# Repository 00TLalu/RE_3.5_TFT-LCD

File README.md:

# RE_3.5_TFT-LCD
 Reverse Engineering PCB 3.5" TFT LCD for arduino uno.

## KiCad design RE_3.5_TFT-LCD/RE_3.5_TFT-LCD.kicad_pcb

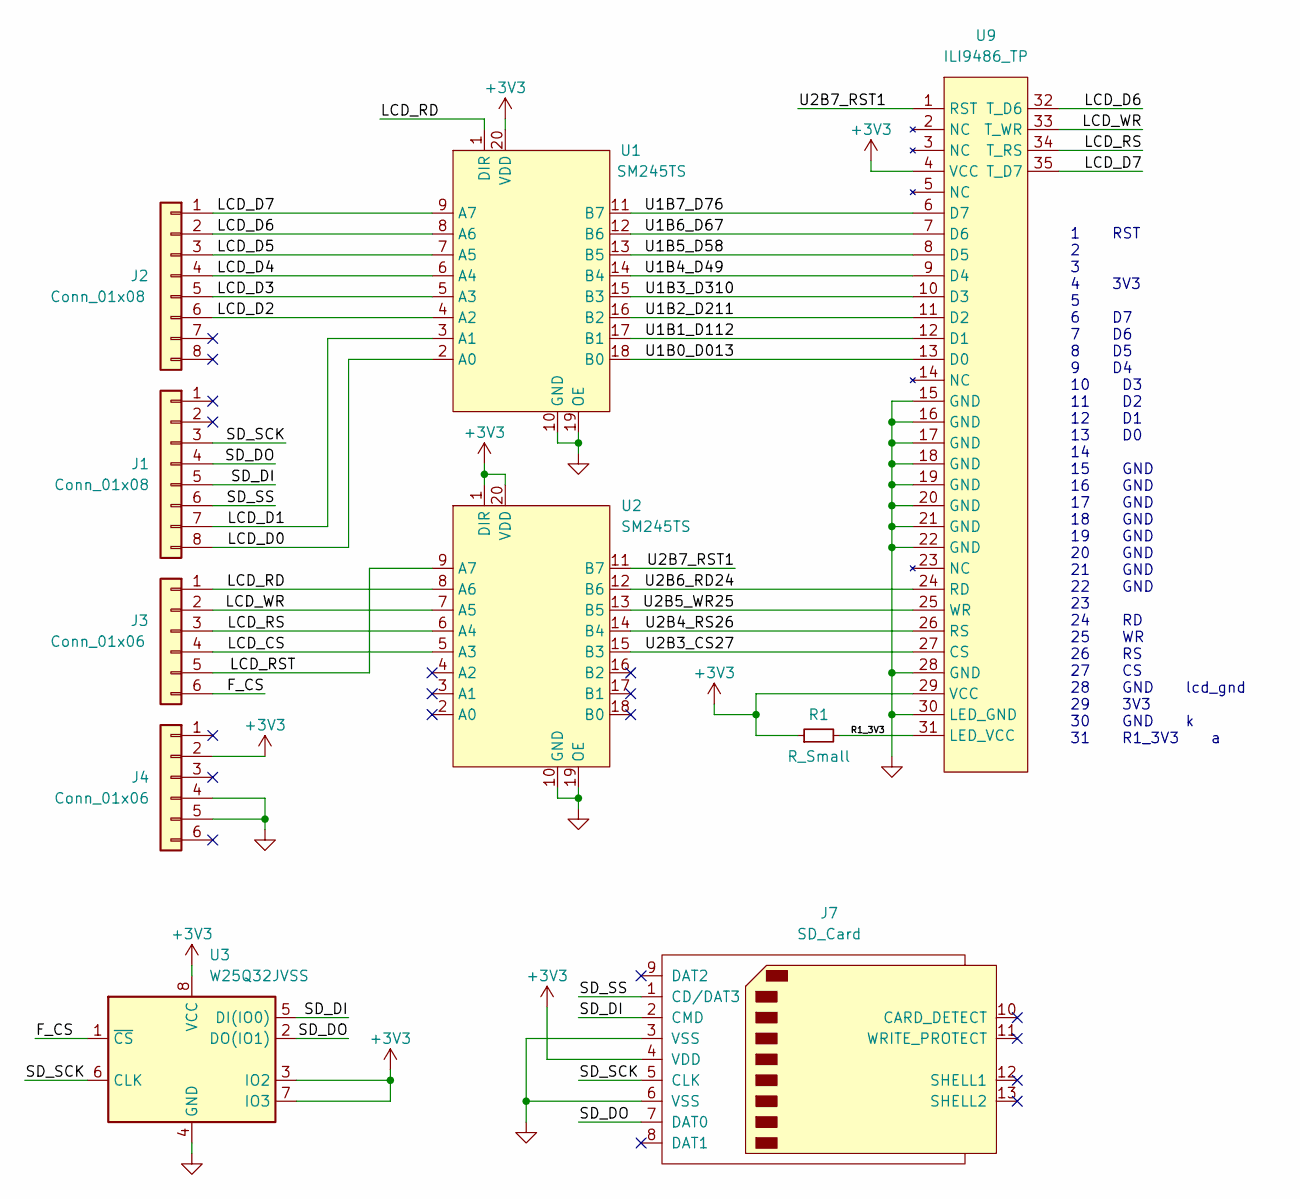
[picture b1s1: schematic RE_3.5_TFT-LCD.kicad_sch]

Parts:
J1, J2: Conn_01x08; PinHeader_1x08_P2.54mm_Vertical
J3, J4: Conn_01x06; PinHeader_1x06_P2.54mm_Vertical
J7: SD_Card; MicroSD
R1: R_Small; R_0402_TL
U1, U2: SM245TS; TSSOP-20_4.4x6.5mm_P0.65mm
U3: W25Q32JVSS; SOIC-8_5.23x5.23mm_P1.27mm_TL
U9: ILI9486_TP; ILI9486_31PIN_3.5_inch_with_TP

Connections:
+3V3: J4.2, J7.4 (VDD), R1.1, U1.20 (VDD), U2.1 (DIR), U2.20 (VDD), U3.3 (IO2), U3.7 (IO3), U3.8 (VCC), U9.4 (VCC), U9.29 (VCC)
/F_CS: J3.6, U3.1 (~CS)
/LCD_CS: J3.4, U2.5 (A3)
/LCD_D0: J1.8, U1.2 (A0)
/LCD_D1: J1.7, U1.3 (A1)
/LCD_D2: J2.6, U1.4 (A2)
/LCD_D3: J2.5, U1.5 (A3)
/LCD_D4: J2.4, U1.6 (A4)
/LCD_D5: J2.3, U1.7 (A5)
/LCD_D6: J2.2, U1.8 (A6), U9.32 (T_D6)
/LCD_D7: J2.1, U1.9 (A7), U9.35 (T_D7)
/LCD_RD: J3.1, U1.1 (DIR), U2.8 (A6)
/LCD_RS: J3.3, U2.6 (A4), U9.34 (T_RS)
/LCD_RST: J3.5, U2.9 (A7)
/LCD_WR: J3.2, U2.7 (A5), U9.33 (T_WR)
/R1_3V3: R1.2, U9.31 (LED_VCC)
/SD_DI: J1.5, J7.2 (CMD), U3.5 (DI(IO0))
/SD_DO: J1.4, J7.7 (DAT0), U3.2 (DO(IO1))
/SD_SCK: J1.3, J7.5 (CLK), U3.6 (CLK)
/SD_SS: J1.6, J7.1 (CD/DAT3)
/U1B0_D013: U1.18 (B0), U9.13 (D0)
/U1B1_D112: U1.17 (B1), U9.12 (D1)
/U1B2_D211: U1.16 (B2), U9.11 (D2)
/U1B3_D310: U1.15 (B3), U9.10 (D3)
/U1B4_D49: U1.14 (B4), U9.9 (D4)
/U1B5_D58: U1.13 (B5), U9.8 (D5)
/U1B6_D67: U1.12 (B6), U9.7 (D6)
/U1B7_D76: U1.11 (B7), U9.6 (D7)
/U2B3_CS27: U2.15 (B3), U9.27 (CS)
/U2B4_RS26: U2.14 (B4), U9.26 (RS)
/U2B5_WR25: U2.13 (B5), U9.25 (WR)
/U2B6_RD24: U2.12 (B6), U9.24 (RD)
/U2B7_RST1: U2.11 (B7), U9.1 (RST)
GND: J4.4, J4.5, J7.3 (VSS), J7.6 (VSS), U1.10 (GND), U1.19 (OE), U2.10 (GND), U2.19 (OE), U3.4 (GND), U9.15 (GND), U9.16 (GND), U9.17 (GND), U9.18 (GND), U9.19 (GND), U9.20 (GND), U9.21 (GND), U9.22 (GND), U9.28 (GND), U9.30 (LED_GND)

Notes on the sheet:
1 RST 2 3 4 3V3 5 6 D7 7 D6 8 D5 9 D4 10 D3 11 D2 12 D1 13 D0 14 15 GND 16 GND 17 GND 18 GND 19 GND 20 GND 21 GND 22 GND 23 24 RD 25 WR 26 RS 27 CS 28 GND lcd_gnd 29 3V3 30 GND k 31 R1_3V3 a

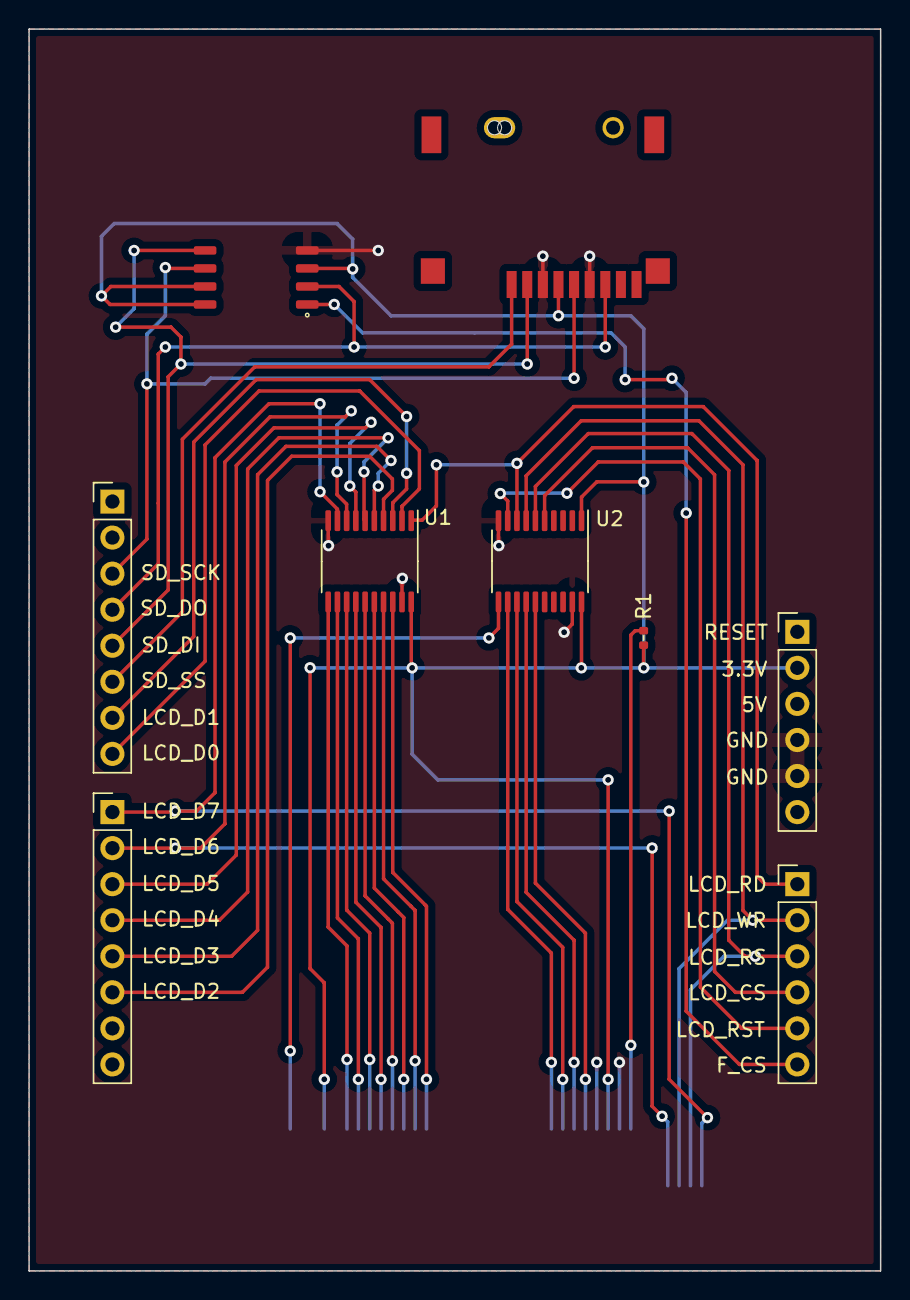
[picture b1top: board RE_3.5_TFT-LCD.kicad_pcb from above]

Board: 2 copper layers, 60.0 x 87.5 mm, 10 parts (1 on the bottom side), 34 nets.

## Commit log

2022-10-05 update_05/10/2022
2022-10-05 add schematic

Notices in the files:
parts and their libraries:
Copyright 2021 Accelerated Designs. All rights reserved.
